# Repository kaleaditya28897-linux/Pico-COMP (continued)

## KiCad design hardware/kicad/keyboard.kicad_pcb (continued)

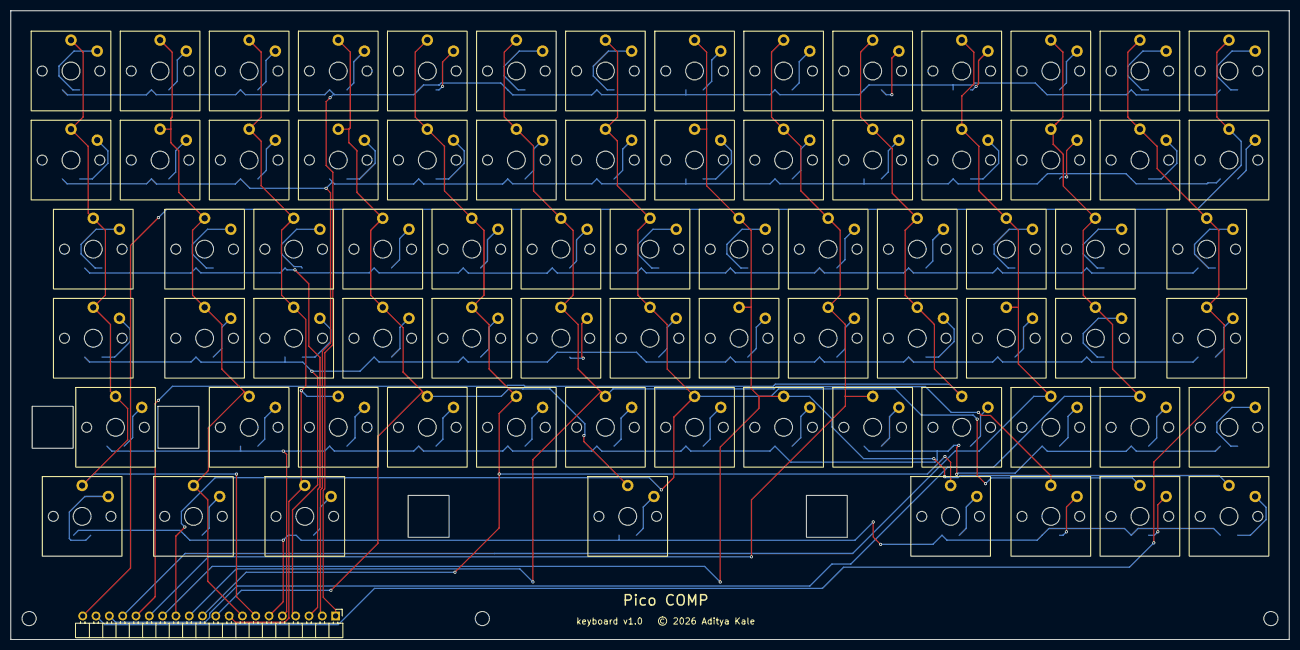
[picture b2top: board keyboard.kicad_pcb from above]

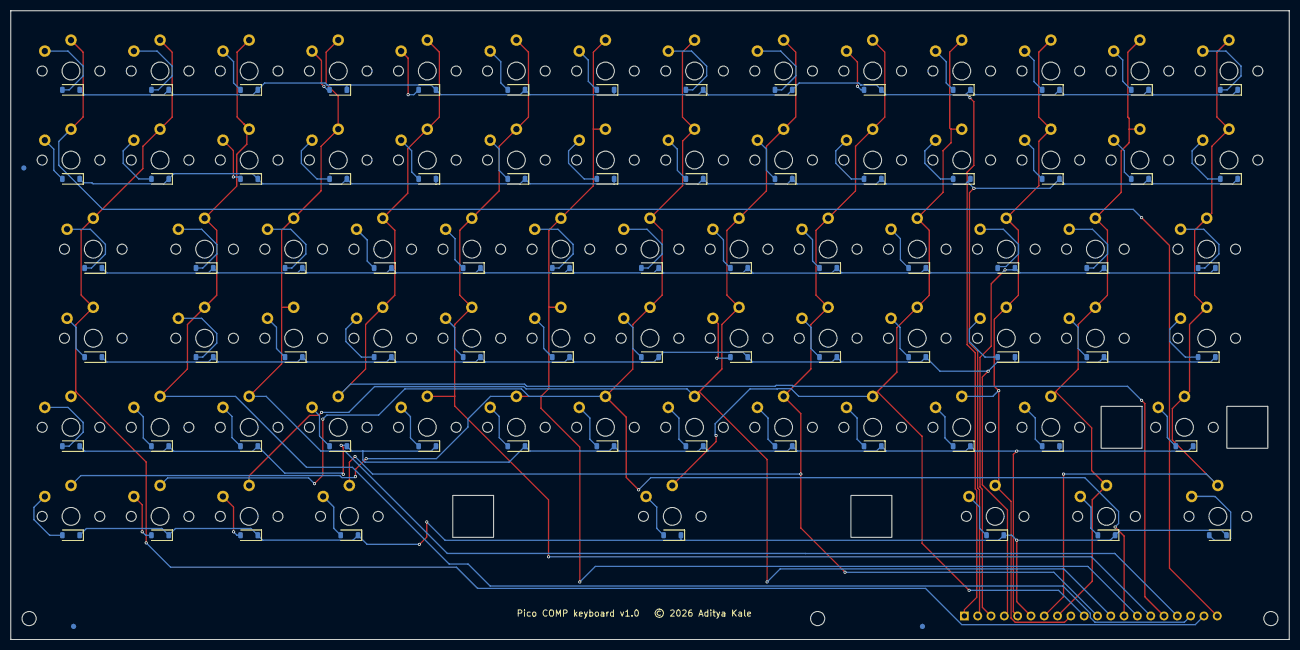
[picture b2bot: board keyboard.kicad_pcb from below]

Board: 2 copper layers, 244.0 x 120.0 mm, 159 parts (78 on the bottom side), 95 nets.

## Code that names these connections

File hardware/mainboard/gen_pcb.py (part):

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    NET_GPIO[r] = f"ROW{r}"
for c in range(14):
    NET_GPIO[6 + c] = f"COL{c}"
NET_GPIO.update({20: "I2C_SDA", 21: "I2C_SCL", 22: "CHG_INT", 23: "WL_ON", 24: "WL_DATA",
                 25: "WL_CS", 26: "WL_CLK", 27: "CHG_STAT", 28: "NET_TX", 29: "NET_RX"})
# UI MCU (U1): expansion 0-3 + 8-11 (I2C0 on 8/9, SPI1 on 8-11), printer UART1 4-7 (TX, RX, CTS, RTS),
# HSTX 12-19, SD SPI0 20-23,
# card detect 24, LED 25, buzzer 26, panel power 27, UART to NET 28/29
# UART0 is the MCU link on 28/29, so the printer uses UART1 (GPIO4 TX, 5 RX, 6 CTS, 7 RTS)
UI_GPIO = {4: "PRN_TX", 5: "PRN_RX", 6: "PRN_CTS", 7: "PRN_RTS"}
EXP_GPIO = [0, 1, 2, 3, 8, 9]
for g in EXP_GPIO:
    UI_GPIO[g] = f"EXP{g}"
# UI GPIO10/11 drive the NET MCU's SWD port: the UI firmware reflashes the NET MCU (one update file)
UI_GPIO.update({10: "NET_SWCLK", 11: "NET_SWDIO"})
# RP2350B extra GPIO: 64 GB eMMC, 4-bit SD/MMC bus via PIO (DAT0-3 consecutive for the PIO program)
# power button sense (through D50, shared with the charger's QON): sleep/wake and soft power-off
UI_GPIO.update({37: "UI_PWR_KEY"})
UI_GPIO.update({30: "EMMC_CLK", 31: "EMMC_CMD", 32: "EMMC_DAT0", 33: "EMMC_DAT1", 34: "EMMC_DAT2",
                35: "EMMC_DAT3", 36: "EMMC_RST"})
UI_GPIO.update({12: "TMDS_D0P", 13: "TMDS_D0N", 14: "TMDS_CKP", 15: "TMDS_CKN",
                16: "TMDS_D2P", 17: "TMDS_D2N", 18: "TMDS_D1P", 19: "TMDS_D1N",
                20: "SD_MISO", 21: "SD_CS", 22: "SD_SCK", 23: "SD_MOSI", 24: "SD_DET",
                25: "UI_LED", 26: "BUZZ", 27: "PANEL_EN", 28: "UI_TX", 29: "UI_RX"})
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

def rp2350(tag, ref, x, y, gpio, usb, part="RP2350A"):
    """part: RP2350A (QFN-60, GPIO0-29) or RP2350B (QFN-80, GPIO0-47)."""
    m = {"IOVDD": "V3V3", "USB_OTP_VDD": "V3V3", "QSPI_IOVDD": "V3V3", "VREG_AVDD": f"{tag}_AVDD",   # RC-filtered (vreg)
         "VREG_VIN": "V3V3", "ADC_AVDD": "V3V3", "DVDD": f"{tag}_1V1", "VREG_FB": f"{tag}_1V1",
         "VREG_LX": f"{tag}_LX", "VREG_PGND": "GND", "GND": "GND",
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            "~{CE}": "GND", "ACDRV1": "GND", "ACDRV2": "GND", "PROG": "PROG", "SDRV": "SDRV", "~{QON}": "QON"},
   mpn="BQ25798RQMR")   # ACDRV to GND: no input FETs. QON = power button (via D50).
# Charger layout (real board mm, fixed=True), after the BQ25798 datasheet layout guide: L5 straight above
# the SW1/SW2 pins with its own switch-node pours; PMID caps on a strip from the PMID pin; BTST caps beside
# the switch pours; REGN cap at its pin; VBUS pour along the left pins (a corridor for the REGN cap); VSYS
# strip from the SYS pin to its caps, then a VSYS area up to the 5 V buck; BAT pour from the BAT pins around
# to the ship FET Q50; VBAT_PACK pour from J2 to Q50's drain. Pours are named PWR_*: the autorouter sees them
# (other nets keep off), so they stay solid.
add("L5", "Inductor_SMD", "L_Bourns_SRP7028A_7.3x6.6mm", 28.0, 23.5, 0, "2.2uH", mpn="SRP7028A-2R2M", fixed=True)
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Cf("C55", "47nF", "BTST2", "SW2", 31.25, 28.25, "0402", 180)    # pad 2 on the SW2 pour
Cf("C50", "10uF", "VBUS", "GND", 18.6, 31.85, "0805", 180)       # VBUS pad (1) on the VBUS pour
Cf("C51", "10uF", "VBUS", "GND", 18.6, 33.95, "0805", 180)
Cf("C56", "4.7uF", "REGN", "GND", 23.9, 32.12, "0603", 180)     # REGN pad (1) next to pin 5
Cf("C57", "10uF", "VSYS", "GND", 33.6, 29.0, "0805", 90)        # VSYS pad (1) down on the VSYS strip
Cf("C58", "10uF", "VSYS", "GND", 35.6, 29.0, "0805", 90)
Cf("C59", "10uF", "VBAT", "GND", 34.55, 33.0, "0805", 0)        # VBAT pad (1) on the BAT column
Cf("C510", "10uF", "VBAT", "GND", 34.55, 35.2, "0805", 0)
track("REGN", (26.10, 32.12), (24.9, 32.12), 0.2)             # REGN pin 5 -> C56
R("R50", "5.23k", "REGN", "TS", 40, 19)
R("R51", "30.1k", "TS", "GND", 40, 21)
R("R52", "47k", "REGN", "ILIM", 40, 23)
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place_edge("J2", "left", 26)
add("J5", "Connector_JST", "JST_PH_B2B-PH-K_1x02_P2.00mm_Vertical", 10, 46, 0, "NTC", mpn="B2B-PH-K-S")
conn("J5", {"1": "TS", "2": "GND"})
track("QON", (27.8, 34.02), (27.8, 35.35), 0.15)                # QON pin 12 -> C512 (straight down)
track("QON", (27.8, 35.35), (27.32, 35.75), 0.15)
track("GND", (28.0, 30.42), (28.0, 29.4), 0.2)                  # GND pin 27 (between SW1 and SW2) -> via
via("GND", (28.0, 29.4), 0.35, 0.15)
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add("J6", "Connector_Video", "HDMI_A_Molex_208658-1001_Horizontal", 0, 0, 90, "HDMI to panel", mpn="2086581001")
conn("J6", {"1": "HD_D2P", "2": "GND", "3": "HD_D2N", "4": "HD_D1P", "5": "GND", "6": "HD_D1N",
            "7": "HD_D0P", "8": "GND", "9": "HD_D0N", "10": "HD_CKP", "11": "GND", "12": "HD_CKN",
            "17": "GND", "18": "V5_PANEL", "SH": "GND"})   # +5V pin 18: sinks need it to see a source
place_edge("J6", "top", 116)
for i, (a, b) in enumerate([("TMDS_D0P", "HD_D0P"), ("TMDS_D0N", "HD_D0N"), ("TMDS_CKP", "HD_CKP"),
                            ("TMDS_CKN", "HD_CKN"), ("TMDS_D2P", "HD_D2P"), ("TMDS_D2N", "HD_D2N"),
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
# Wi-Fi: Raspberry Pi RM2 (CYW43439, onboard antenna), wired like the Pico 2 W (RM2 datasheet Table 1/2).
# Rotated 180 so the antenna end sits flush on the front board edge; its RF keep-out (in the footprint)
# hangs off the board. Firmware: CYW43 pins WL_ON=23, DATA=24, CS=25, CLK=26 (NET MCU).
add("U8", LOCAL_LIB, "RaspberryPi_RM2", 85, BH - 8.25, 180, "RM2", mpn="RMC20452T", fixed=True)
SYMBOL["U8"] = (LOCAL_LIB, "RaspberryPi_RM2")
conn("U8", {"1": "GND", "4": "GND", "7": "GND", "11": "GND", "15": "GND", "21": "GND",
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add("J12", "Connector_JST", "JST_SH_SM06B-SRSS-TB_1x06-1MP_P1.00mm_Horizontal", 140, 64, 0, "PRINTER", mpn="SM06B-SRSS-TB")
conn("J12", {"MP": "GND", "1": "V5", "2": "PRN_TX", "3": "PRN_RX", "4": "PRN_RTS", "5": "PRN_CTS", "6": "GND"})
add("J13", "Connector_PinHeader_1.27mm", "PinHeader_1x10_P1.27mm_Vertical", 120, 62, 90, "EXPANSION", spec="1x10 1.27 mm header")
conn("J13", {"1": "V3V3", "2": "GND", **{str(3 + i): f"EXP{g}" for i, g in enumerate(EXP_GPIO)}, "9": "GND", "10": "V3V3"})

# UI reset on the right edge, side-actuated, behind a pinhole in the case wall. Double-tap = USB update
# mode (pico_bootsel_via_double_reset in the UI firmware).
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conn("D51", {"1": "UI_RUN", "2": "NET_RUN", "3": "SYS_RST"})

# Power button: right wall, above the reset pinhole, finger-pressed through a printed plunger in the case.
# It pulls the charger's QON (exit ship mode / 10 s system power cycle) and UI GPIO37 (short presses:
# sleep, wake, soft power-off) low through D50. QON's internal pull-up reaches 3.8 V, so the diode keeps
# it off the 3.3 V GPIO; with the system off (ship mode) the GPIO side is unpowered and blocks too.
add("SW5", "Button_Switch_SMD", "Panasonic_EVQPUJ_EVQPUA", 0, 0, 270, "POWER", mpn="EVQ-PUJ02K")
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ic("U11", "Package_TO_SOT_SMD", "SOT-23-6", ("Power_Protection", "USBLC6-2SC6"), 136, 54, {
    "I/O1": "NET_USB_P", "GND": "GND", "I/O2": "NET_USB_N", "VBUS": "VBUS2"}, value="USBLC6-2SC6", mpn="USBLC6-2SC6")

# 64 GB eMMC 5.1 (JEDEC 153-ball FBGA) below the UI MCU, 4-bit bus on GPIO30-36. VCC and VCCQ both 3.3 V.
# Ball map + pull-up / VDDi values: Kimtigo KM110SS1064GxA datasheet (CMD 4.7-100k, DAT 10-100k, VDDi 1 uF).
# Fab: the 0.5 mm-pitch balls use via-in-pad (filled + capped), placed by fanout.py.
EMMC_X, EMMC_Y = 99.6, 70.5                      # real board coords: right of the RM2, below the UI MCU
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add("D2", "LED_SMD", "LED_0603_1608Metric", 129, 59.5, 0, "UI", spec="LED green 0603")
conn("D2", {"1": "GND", "2": "UI_LEDK"})

# Beeper: piezo driven straight from GPIO26 (PWM) through 100R
add("BZ1", "Buzzer_Beeper", "Buzzer_Murata_PKMCS0909E", 128, 30, 0, "Piezo", mpn="PKMCS0909E4000-R1")
conn("BZ1", {"1": "BUZZ_R", "2": "GND"})
R("R98", "100", "BUZZ", "BUZZ_R", 128, 36)
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
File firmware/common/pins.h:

#ifndef COMP_PINS_H
#define COMP_PINS_H

/* GPIO map of the main board (hardware/mainboard/gen_pcb.py is the source of truth).
 *
 * Firmware updates: one .uf2 on the UI MCU (USB-C, BOOTSEL drive mode via an "update" hotkey,
 * reset_usb_boot(), or a double tap of the pinhole RESET button). The UI image carries the NET MCU
 * image and writes it over SWD (UI_PIN_NET_SWCLK/SWDIO) when the NET version differs. The NET MCU's
 * own USB is on USB-C port 2 (J14, factory / recovery flashing).
 *
 * Buttons (right wall):
 *  - POWER (SW5): pulls the BQ25798's QON and UI GPIO37 low through a dual diode. Short press: firmware
 *    event (sleep / wake / ask to power off). Power off = NET writes SDRV_CTRL = 10 (REG0x0F bits 2:1, ship
 *    mode): the ship FET Q50 disconnects the pack. Power on = press >= 1 s (15 ms if WKUP_DLY = 1) or plug
 *    in USB. Holding it 10 s power-cycles everything in hardware (BQ25798 tRST), even if firmware hangs.
 *  - RESET pinhole (SW2): resets both MCUs at once (UI_RUN and NET_RUN through a dual diode).
 *    Double tap = UI USB update mode (pico_bootsel_via_double_reset). */

/* ---- UI MCU (U1) ---- */
#define UI_PIN_EXP_0_3   0   /* expansion header J13 pins 3-6 = GPIO0-3 */
#define UI_PIN_PRN_TX    4   /* printer UART1 TX (UART0 is the MCU link) */
#define UI_PIN_PRN_RX    5   /* printer UART1 RX */
#define UI_PIN_PRN_CTS   6   /* printer UART1 CTS */
#define UI_PIN_PRN_RTS   7   /* printer UART1 RTS */
#define UI_PIN_EXP_8_9   8   /* expansion header J13 pins 7-8 = GPIO8-9 (I2C0); pins 9/10 = GND/3V3 */
#define UI_PIN_NET_SWCLK 10  /* UI drives the NET MCU's SWD port: the UI firmware reflashes the NET MCU */
#define UI_PIN_NET_SWDIO 11
#define UI_PIN_TMDS_FIRST 12 /* HSTX: D0 12/13, CK 14/15, D2 16/17, D1 18/19 (see dvi_text.c) */
#define UI_PIN_SD_MISO   20  /* SPI0 */
#define UI_PIN_SD_CS     21
#define UI_PIN_SD_SCK    22
#define UI_PIN_SD_MOSI   23
#define UI_PIN_SD_DET    24  /* card detect switch to GND, needs pull-up */
#define UI_PIN_LED       25
#define UI_PIN_BUZZER    26  /* piezo via 100R: drive with PWM (~4 kHz resonance) */
#define UI_PIN_PANEL_EN  27  /* TPS22917 panel 5 V switch, high = on (100k pull-down) */
/* RP2350B only (UI MCU): 64 GB eMMC, 4-bit SD/MMC bus driven by PIO (DAT0-3 consecutive) */
#define UI_PIN_EMMC_CLK  30
#define UI_PIN_EMMC_CMD  31
#define UI_PIN_EMMC_DAT0 32  /* DAT1-3 = 33-35 */
#define UI_PIN_EMMC_RST  36  /* active low, 10k pull-up */
#define UI_PIN_PWR_KEY   37  /* power button, active low (10k pull-up; shared with charger QON via D50) */
#define UI_PIN_LINK_TX   28  /* UART0 TX to NET RX 29 */
#define UI_PIN_LINK_RX   29

/* ---- NET MCU (U2) ---- */
#define NET_PIN_ROW_FIRST 0  /* ROW0-5 = GPIO0-5: drive low one at a time */
#define NET_PIN_COL_FIRST 6  /* COL0-13 = GPIO6-19: inputs with pull-ups (diode anode on the column side) */
#define NET_PIN_I2C_SDA  20  /* I2C0 to BQ25798 (address 0x6B) */
#define NET_PIN_I2C_SCL  21
#define NET_PIN_CHG_INT  22  /* BQ25798 INT, open drain, active low */
#define NET_PIN_WL_ON    23  /* RM2 WL_ON + BT_ON */
#define NET_PIN_WL_DATA  24  /* RM2 gSPI data (DIN direct, DOUT via 470R, IRQ via 10k) */
#define NET_PIN_WL_CS    25
#define NET_PIN_WL_CLK   26  /* differs from the Pico 2 W (29): override CYW43_DEFAULT_PIN_WL_CLOCK */
#define NET_PIN_CHG_STAT 27  /* BQ25798 STAT */
#define NET_PIN_LINK_TX  28  /* to UI RX 29 */
#define NET_PIN_LINK_RX  29

#endif
